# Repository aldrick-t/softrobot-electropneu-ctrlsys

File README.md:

# softrobot-electropneu-ctrlsys
Control elements for pneumatic actuated soft robots. Including microcontroller controller firmware, controller PCBs, control board use guidelines and more.

## Closed-loop vacuum controller

This PlatformIO firmware regulates a negative-pressure pneumatic circuit with
an ESP32 DevKit V1, a vacuum-pump motor, a solenoid valve, an ADS1115 ADC, and
a 5 V XGZP6847A pressure sensor. It is set up for the installed
`XGZP6847A100KPGPN` variant: its nominal 0.5–4.5 V output represents −100 to
+100 kPa gauge pressure. The controller only commands negative pressure.

### Hardware and signal path

| Function | Connection | Firmware behavior |
| --- | --- | --- |
| Pump motor PWM | ESP32 GPIO 2 | `0` is off; `255` is full duty cycle. |
| Solenoid valve | ESP32 GPIO 5 | HIGH opens the pump-to-gripper path; LOW de-energizes the valve and vents the gripper. |
| Target-reached LED1 (green) | ESP32 GPIO 12 through 220 Ω to GND | On only when serial closed-loop pressure is within the configured deadband. |
| Active LED2 | ESP32 GPIO 13 through 220 Ω to GND | On when firmware commands nonzero pump PWM or energizes the valve. |
| Mode switch: manual full | ESP32 GPIO 26 with 1 kΩ pulldown | 3.3 V selects pump PWM `255` and valve open. |
| Mode switch: serial control | ESP32 GPIO 27 with 1 kΩ pulldown | 3.3 V enables serial closed-loop control. |
| ADS1115 SDA | ESP32 GPIO 21 through the 3.3 V/5 V I2C level shifter | Initialized with `Wire.begin(21, 22)`. |
| ADS1115 SCL | ESP32 GPIO 22 through the 3.3 V/5 V I2C level shifter | Initialized with `Wire.begin(21, 22)`. |
| XGZP6847A output | ADS1115 A0 | Read as a 5 V-domain analog signal; it never connects directly to the ESP32. |

The ADC uses its ±6.144 V range (`GAIN_TWOTHIRDS`), so the sensor's 0.5–4.5 V
signal cannot clip. After field zeroing, the nominal conversion is:

```text
pressure_kPa = 50 × (sensor_volts − zero_volts)
```

`ZERO` removes the atmospheric offset; it does not replace a calibrated span
check against a reference gauge.

## Operation

With the pressure port open to atmosphere, first send:

```text
ZERO
```

The controller turns both outputs off for one second, then averages 32 stable
pressure samples. Do not obstruct the vent or run the pump while it calibrates.

After `ZERO complete`, send a negative gauge-pressure target as a bare number:

```text
-20
-65.93
```

The accepted range is −90 to 0 kPa. Values below −90 kPa clamp to −90; positive
values clamp to zero and vent. Any zero representation stops control and vents:

```text
0
0.0
-0.0
```

### Serial commands

| Command | Effect |
| --- | --- |
| `ZERO` | In serial mode, vent, establish atmospheric offset, and permit negative targets. Required after every reboot. |
| `STATUS` | Print controller state, mode, voltage, pressure, target, PWM, valve state, LED states, ADC address, calibration state, and tuning. |
| `STATUS_STREAM` | Toggle continuous `STATUS` output at 20 Hz. Send `STATUS_STREAM` again to stop it. |
| `KP <value>` | Set proportional gain in RAM; allowed range 0–50. |
| `KI <value>` | Set integral gain in RAM; allowed range 0–20. |
| `KD <value>` | Set derivative damping gain in RAM; allowed range 0–10. |
| `BAND <kPa>` | Set deadband in RAM; allowed range 0.1–5 kPa. |
| `SAVE` | Persist current validated tuning in ESP32 Preferences. |
| `DEFAULTS` | Restore conservative default tuning in RAM; send `SAVE` to retain it after reboot. |

Malformed commands stop active control and vent as a precaution.

## Controller behavior

The loop runs every 50 ms and averages four ADS1115 readings per update. PID
control uses anti-windup, a filtered pressure-rate term, and a PWM slew limit.

- If pressure is not negative enough, the valve opens to the pump and PWM rises
  gradually.
- At or beyond the target deadband, the pump turns off while the valve remains
  on the pump-to-gripper path. The controller does not use the full-flow
  atmosphere vent as a corrective actuator.
- Passive venting (valve off) remains the safety/release path for `0`, faults,
  malformed commands, and `ZERO`.

This checkout's defaults are `KP=18`, `KI=1`, `KD=0.3`, and `BAND=0.5 kPa`.
Tune them on the real pump, tubing volume, valve flow, and gripper before
relying on them. In particular, confirm that valve-on/pump-off holds vacuum
without overheating a non-continuous-duty valve coil.

### Switch modes and LEDs

The SPDT mode switch is the output authority. The firmware reads both switch
inputs on every loop and accepts only these complementary states:

| GPIO 26 | GPIO 27 | Mode | Output behavior |
| --- | --- | --- | --- |
| HIGH | LOW | Manual full-drive | Pump PWM is `255` and the valve is energized, even if the ADS1115 is unavailable or faulted. Entering this mode cancels any serial target or calibration in progress. LED2 is on; LED1 is off. |
| LOW | HIGH | Serial closed-loop | The controller remains vented/idle until a new negative serial target is sent. Existing ADC, `ZERO`, target-range, and fault checks apply. |
| LOW | LOW | Safe off | Pump and valve are de-energized. |
| HIGH | HIGH | Safe off | Pump and valve are de-energized. |

Returning from manual full-drive to serial mode does not restore an earlier
target; send `ZERO` if needed, then a new negative target. In manual or
safe-off mode, `ZERO` and numeric target commands are rejected. `STATUS`,
tuning commands, `SAVE`, and `DEFAULTS` remain available.

LED1 is off while the controller ramps, vents, settles, calibrates, idles, is
faulted, or is in manual/safe-off mode. LED2 represents **commanded drive**:
it cannot prove that a disconnected, stalled, or failed motor/valve is drawing
current because this board has no current-sense circuit.

### ADS1115 ADDR override

For reliable normal operation, wire ADS1115 `ADDR` to GND and use I2C address
`0x48`. The ADS1115 samples this address-selection pin continuously, so a
floating pin is not dependable.

For initial bench testing, `src/main.cpp` includes:

```cpp
const bool ALLOW_FLOATING_ADS1115_ADDR_FOR_TESTING = true;
```

With this temporary toggle enabled, firmware first tries `0x48`, then the
other legal ADS1115 addresses (`0x49`, `0x4A`, `0x4B`). It prints a warning if
the ADC is found away from `0x48`; `STATUS` also reports `ADS_ADDR`. This only
accommodates an accidentally stable floating pin. After wiring `ADDR → GND`,
set this toggle to `false` and rebuild.

## Installation and upload

1. Install [PlatformIO for VS Code](https://platformio.org/install/ide?install=vscode)
   and open this repository as a PlatformIO project.
2. Confirm `platformio.ini` targets `esp32doit-devkit-v1`.
3. Build. PlatformIO installs `Adafruit ADS1X15` automatically; `Arduino`,
   `Wire`, and ESP32 `Preferences` are framework libraries.

   ```sh
   pio run
   ```

4. Connect the ESP32 by USB and upload:

   ```sh
   pio run --target upload
   ```

5. Open a serial monitor at **115200 baud** with line ending set to `Newline`:

   ```sh
   pio device monitor --baud 115200
   ```

Boot starts deliberately uncalibrated. The firmware leaves the pump and valve
off and rejects negative targets until `ZERO` succeeds.

## Idle, off, and fault behavior

The firmware commands **both motor and valve off electrically** when it
is idle or at atmospheric pressure:

```cpp
setOutputs(PWM_OFF, false);
// pump:  analogWrite(GPIO 2, 0)
// valve: analogWrite(GPIO 5, 0)
```

This output path is used at boot, after `0`, after a positive target clamps to
zero, after malformed input, during zeroing, on pressure/ADC faults, and for
invalid mode-switch states. The D26 manual-full mode is the explicit exception:
it deliberately drives both outputs even with a sensor fault. With the stated
plumbing, valve-off is also the pneumatic vent state; it does not attempt to
hold vacuum. Therefore the valve coil is not intentionally kept energized while
idle, avoiding prolonged activation and overheating.

This conclusion assumes a non-inverting valve driver where GPIO 5 HIGH
energizes the coil, as defined by the original controller. Confirm that once
with a multimeter or indicator LED before connecting a gripper.

## First physical test

1. Test with the gripper disconnected or a conservative vented fixture.
2. Select serial mode (GPIO 27 HIGH) and send `STATUS`; verify `MODE=SERIAL`,
   `PWM=0`, `VALVE=VENT`, `LED1=OFF`, `LED2=OFF`, and `ZERO=REQUIRED`.
3. Run `ZERO` with the port open to atmosphere. If possible, compare reported
   voltage with a multimeter at ADS1115 A0.
4. Start with `-5`, then `-10`; verify motor PWM ramps rather than jumps,
   LED2 is on while the pump or valve is commanded, and LED1 turns on only
   after pressure reaches the configured deadband.
5. Send `0` and verify both PWM outputs and both LEDs are off before longer tests.
6. Select manual full-drive (GPIO 26 HIGH) and verify `PWM=255`, `VALVE=OPEN`,
   LED2 on, and LED1 off. Return to serial mode and verify it remains vented
   until a new negative target is sent.
7. Verify both-low and both-high switch input states keep both outputs and LEDs off.
8. Tune one variable at a time and send `SAVE` only after physical validation.

Never treat the −90 kPa software clamp as proof that the gripper, tubing,
fittings, or pump are safe at that pressure.

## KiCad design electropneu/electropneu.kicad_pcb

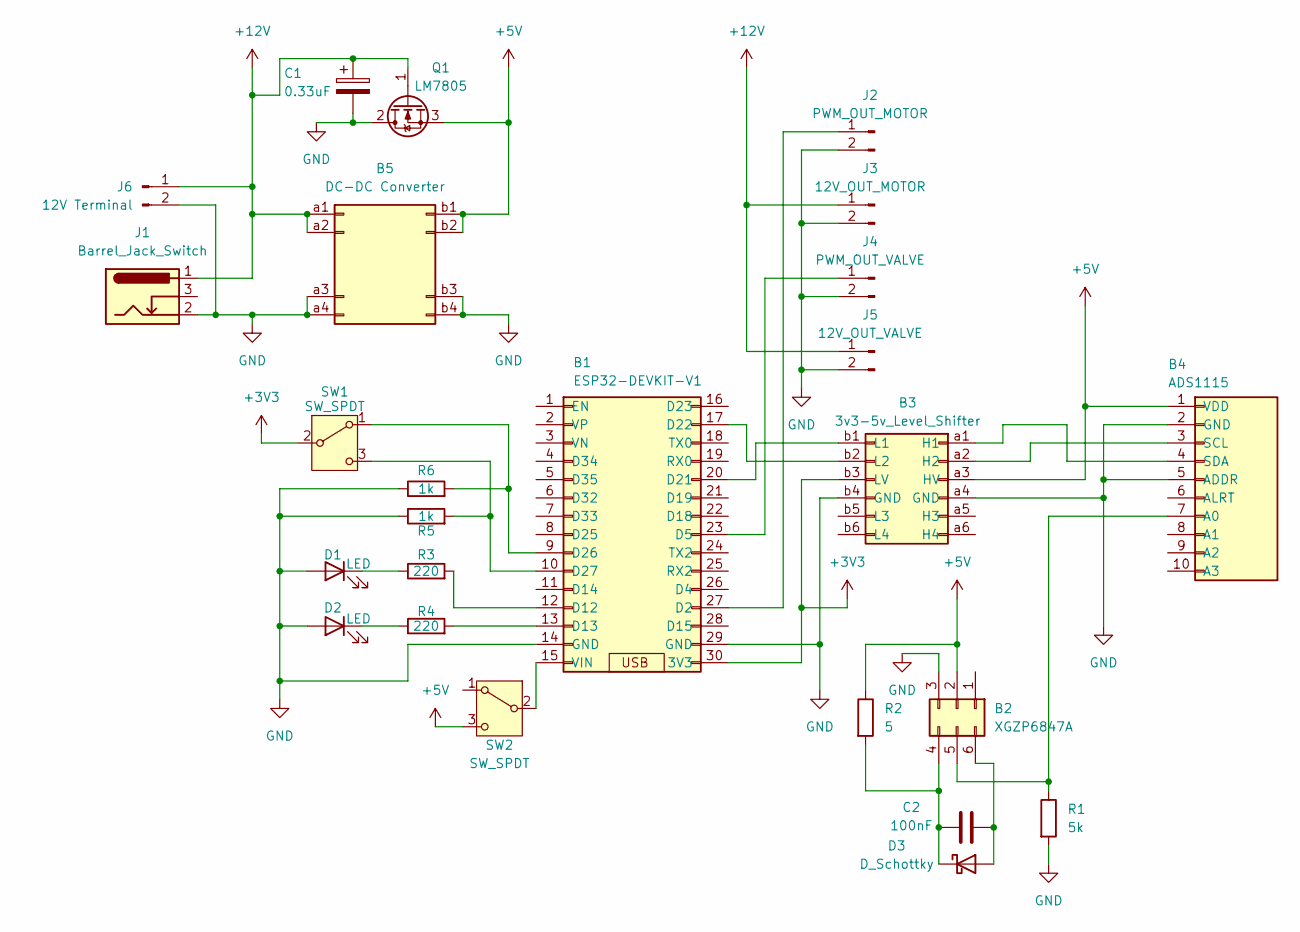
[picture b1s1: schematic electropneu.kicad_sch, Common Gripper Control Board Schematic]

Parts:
B1: ESP32-DEVKIT-V1
B2: XGZP6847A; XGZP6847A Sensor Board
B3: 3v3-5v_Level_Shifter; LevelShifter_3V3-5V
B4: ADS1115; ADS1115 Board
B5: DC-DC Converter; MP1584EN Board
C1: 0.33uF; C_Radial_D4.0mm_H5.0mm_P1.50mm
C2: 100nF; C_Rect_L11.0mm_W3.4mm_P10.00mm_MKT
D1, D2: LED; LED_D5.0mm
D3: D_Schottky; D_DO-34_SOD68_P7.62mm_Horizontal
J1: Barrel_Jack_Switch; BarrelJack_Horizontal
J2: PWM_OUT_MOTOR; TerminalBlock_Phoenix_MKDS-1,5-2-5.08_1x02_P5.08mm_Horizont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
J3: 12V_OUT_MOTOR; TerminalBlock_Phoenix_MKDS-1,5-2-5.08_1x02_P5.08mm_Horizont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
J4: PWM_OUT_VALVE; TerminalBlock_Phoenix_MKDS-1,5-2-5.08_1x02_P5.08mm_Horizont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
J5: 12V_OUT_VALVE; TerminalBlock_Phoenix_MKDS-1,5-2-5.08_1x02_P5.08mm_Horizont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
J6: 12V Terminal; TerminalBlock_Phoenix_MKDS-1,5-2-5.08_1x02_P5.08mm_Horizont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
Q1: LM7805; TO-220-3_Vertical
R1: 5k; R_Axial_DIN0414_L11.9mm_D4.5mm_P15.24mm_Horizontal
R2: 5; R_Axial_DIN0414_L11.9mm_D4.5mm_P15.24mm_Horizontal
R3, R4: 220; R_Axial_DIN0207_L6.3mm_D2.5mm_P10.16mm_Horizontal
R5, R6: 1k; R_Axial_DIN0207_L6.3mm_D2.5mm_P10.16mm_Horizontal
SW1, SW2: SW_SPDT; PinHeader_1x03_P2.54mm_Vertical

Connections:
+3V3: B1.30 (3V3), B3.b3 (LV), SW1.2 (B)
+5V: B2.2, B3.a3 (HV), B4.1 (VDD), B5.b1, B5.b2, Q1.3 (S), R2.1, SW2.3 (C)
+12V: B5.a1, B5.a2, C1.1, J1.1, J3.1, J5.1, J6.1, Q1.1 (G)
GND: B1.14 (GND), B1.29 (GND), B2.3, B3.a4 (GND), B3.b4 (GND), B4.2 (GND), B4.5 (ADDR), B5.a3, B5.a4, B5.b3, B5.b4, C1.2, D1.2 (A), D2.2 (A), J1.2, J2.2, J3.2, J4.2, J5.2, J6.2, Q1.2 (D), R1.2, R5.1, R6.1
unnamed: B1.27 (D2), J2.1
unnamed: B1.23 (D5), J4.1
unnamed: B1.12 (D12), R3.2
unnamed: B1.13 (D13), R4.2
unnamed: B1.20 (D21), B3.b1 (L1)
unnamed: B1.17 (D22), B3.b2 (L2)
unnamed: B1.9 (D26), R6.2, SW1.1 (A)
unnamed: B1.10 (D27), R5.2, SW1.3 (C)
unnamed: B1.15 (VIN), SW2.2 (B)
unnamed: B2.4, C2.1, D3.1 (K), R2.2
unnamed: B2.5, B4.7 (A0), R1.1
unnamed: B2.6, C2.2, D3.2 (A)
unnamed: B3.a1 (H1), B4.4 (SDA)
unnamed: B3.a2 (H2), B4.3 (SCL)
unnamed: D1.1 (K), R3.1
unnamed: D2.1 (K), R4.1

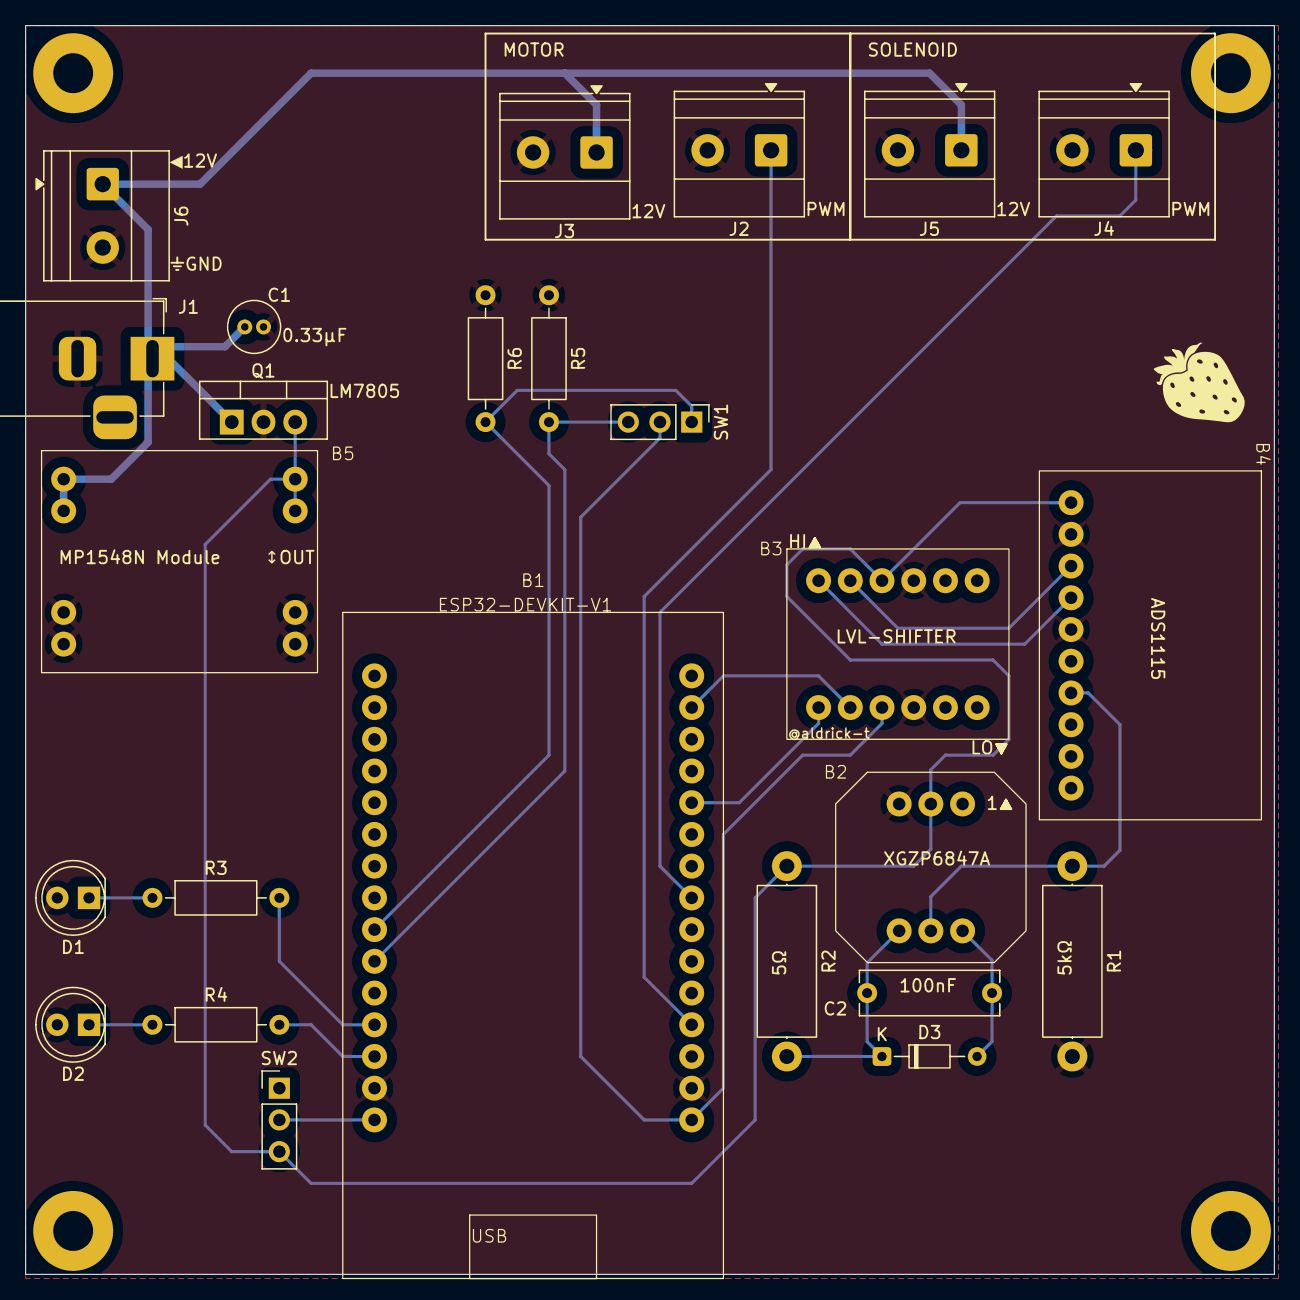
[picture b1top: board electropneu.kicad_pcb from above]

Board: 2 copper layers, 100.0 x 100.0 mm, 25 parts (0 on the bottom side), 20 nets.

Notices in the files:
electropneu/electropneu.kicad_pcb:
aldrick-t, ©2026
